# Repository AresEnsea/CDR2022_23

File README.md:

## Ce git contient les projets CubeIDE suivant : 
* Code pour F446RE principale utilisé à la coupe avec un bug pour la marche arrière "PhobosBoardWifiAndStratV2" 2A/Com/PhobosBoardWifiAndStratV2
* Code pour F446RE secondaire où la marche arrière fonctionne mais le code pour le lidar doit être ajouté "PhobosMainBoard" 2A/Com/PhobosMainBoard
* Code pour F303K8 gérant les actionneur "Project_Ax12" 2A/Project_Ax12
* Code pour G0 gérant le lidar "LIDAR_Ares_v1_4" 2A/Detection/LIDAR_Ares_v1_4
* Code pour F746 discovery kit de l'ihm "Final" 2A/Affichage/Final

## Le git est répartie en plusieurs fichiers :
* 2A/Com pour tout ce qui est lié à la communication sans fil
* 2A/Affichage pour l'ihm
*

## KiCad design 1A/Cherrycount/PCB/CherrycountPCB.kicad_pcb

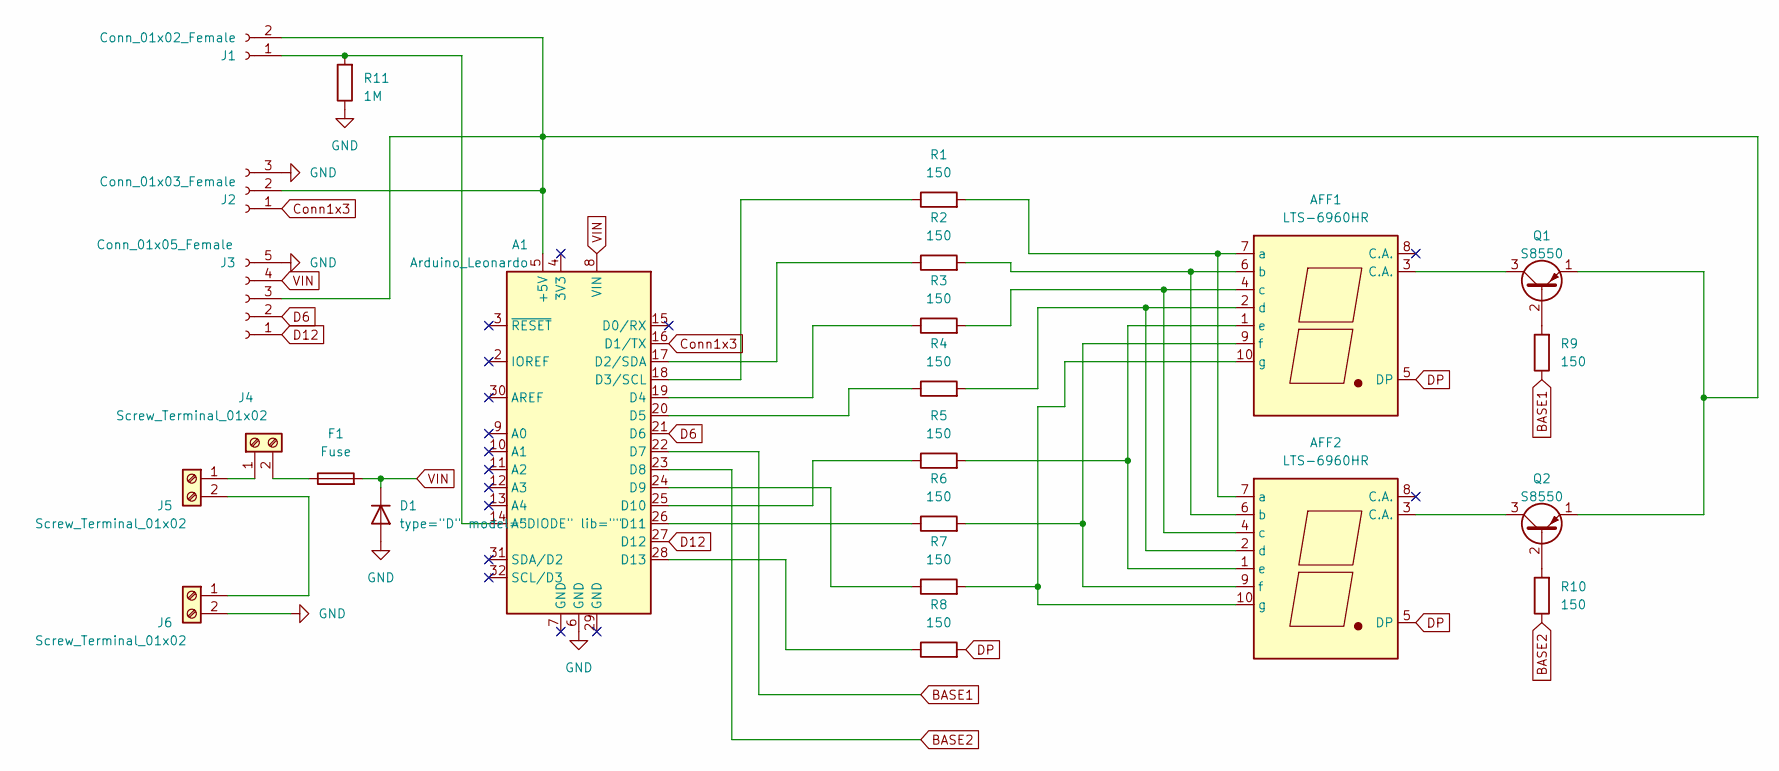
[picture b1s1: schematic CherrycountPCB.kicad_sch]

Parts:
A1: Arduino_Leonardo; Arduino_UNO_R3
AFF1, AFF2: LTS-6960HR; 7seg
D1: type="D" model="DIODE" lib=""; D_DO-41_SOD81_P7.62mm_Horizontal
F1: Fuse; polyswitch
J1: Conn_01x02_Female; PinHeader_1x02_P2.54mm_Vertical
J2: Conn_01x03_Female; PinHeader_1x03_P2.54mm_Vertical
J3: Conn_01x05_Female; PinHeader_1x05_P2.54mm_Vertical
J4, J5, J6: Screw_Terminal_01x02; 180G-2-vertical
Q1, Q2: S8550; TO-92_Inline
R1, R2, R3, R4, R5, R6, R7, R8, R9, R10: 150; R_0805_2012Metric_Pad1.20x1.40mm_HandSolder
R11: 1M; R_0805_2012Metric_Pad1.20x1.40mm_HandSolder

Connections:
BASE1: A1.22 (D7), R9.1
BASE2: A1.23 (D8), R10.1
Conn1x3: A1.16 (D1/TX), J2.1
D6: A1.21 (D6), J3.2
D12: A1.27 (D12), J3.1
DP: AFF1.5 (DP), AFF2.5 (DP), R8.2
GND: A1.6 (GND), D1.1 (A), J2.3, J3.5, J6.2, R11.1
unnamed: A1.5 (+5V), J1.2, J2.2, J3.3, Q1.1 (E), Q2.1 (E)
unnamed: A1.14 (A5), J1.1, R11.2
unnamed: A1.17 (D2/SDA), R2.1
unnamed: A1.18 (D3/SCL), R1.1
unnamed: A1.19 (D4), R3.1
unnamed: A1.20 (D5), R4.1
unnamed: A1.24 (D9), R7.1
unnamed: A1.25 (D10), R5.1
unnamed: A1.26 (D11), R6.1
unnamed: A1.28 (D13), R8.1
unnamed: AFF1.7 (a), AFF2.7 (a), R1.2
unnamed: AFF1.6 (b), AFF2.6 (b), R2.2
unnamed: AFF1.4 (c), AFF2.4 (c), R3.2
unnamed: AFF1.2 (d), AFF2.2 (d), R4.2
unnamed: AFF1.1 (e), AFF2.1 (e), R5.2
unnamed: AFF1.9 (f), AFF2.9 (f), R6.2
unnamed: AFF1.10 (g), AFF2.10 (g), R7.2
unnamed: J4.1, J5.1
unnamed: F1.1, J4.2
unnamed: J5.2, J6.1
unnamed: Q1.2 (B), R9.2
unnamed: AFF1.3 (C.A.), Q1.3 (C)
unnamed: Q2.2 (B), R10.2
unnamed: AFF2.3 (C.A.), Q2.3 (C)
VIN: A1.8 (VIN), D1.2 (K), F1.2, J3.4

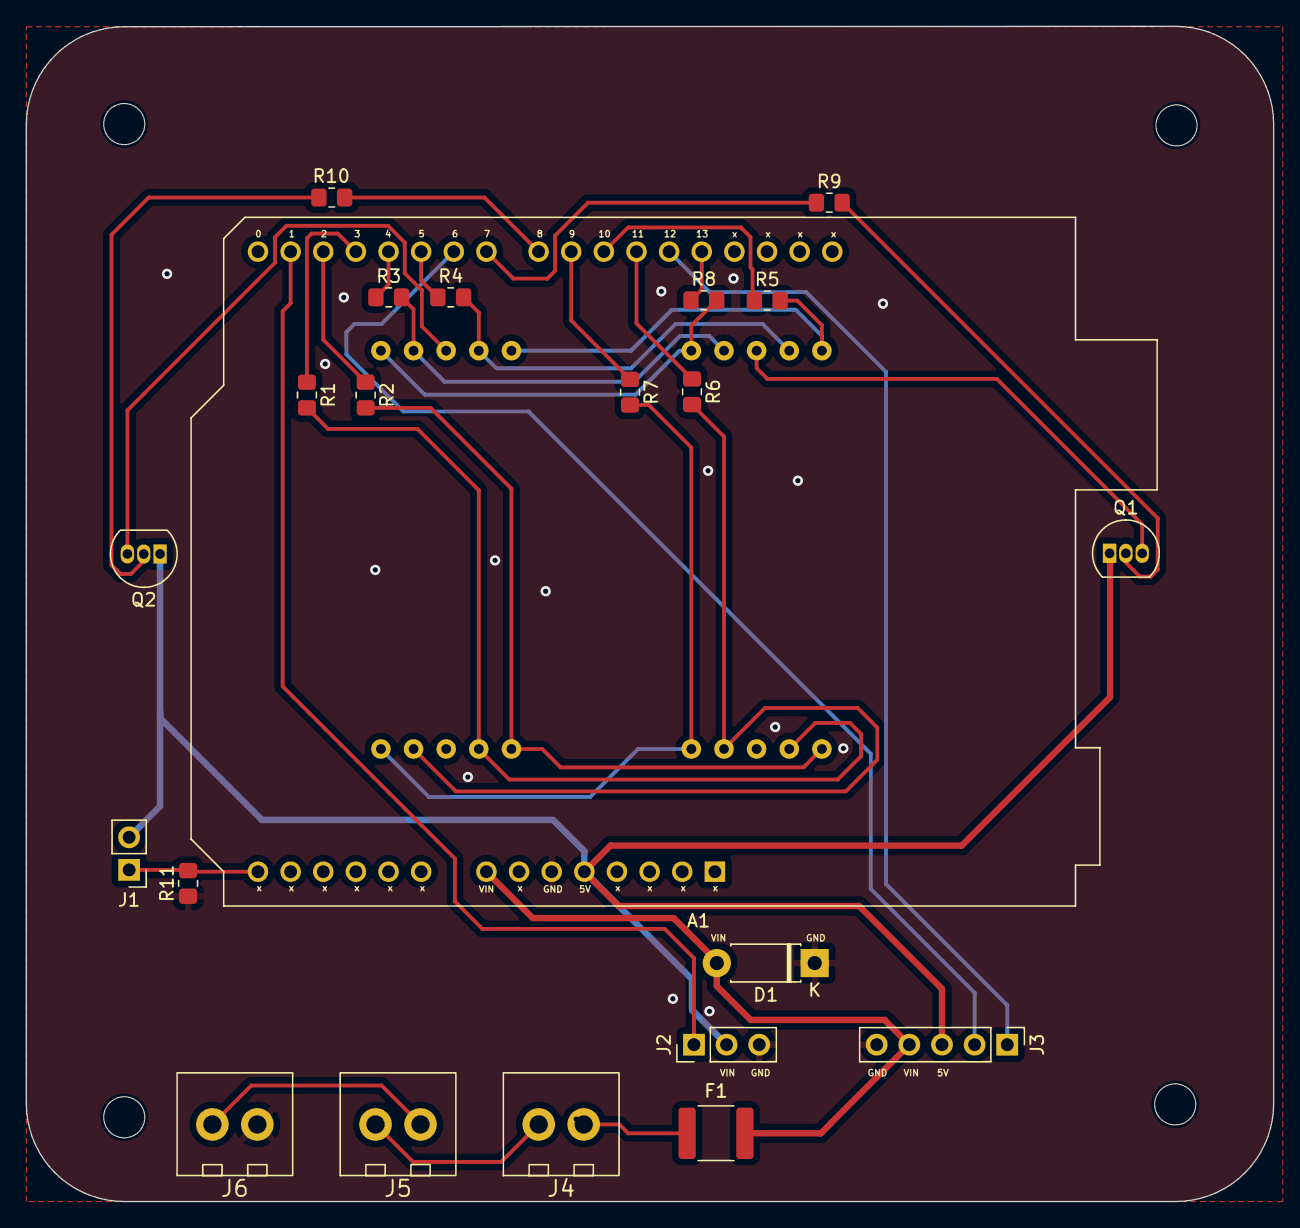
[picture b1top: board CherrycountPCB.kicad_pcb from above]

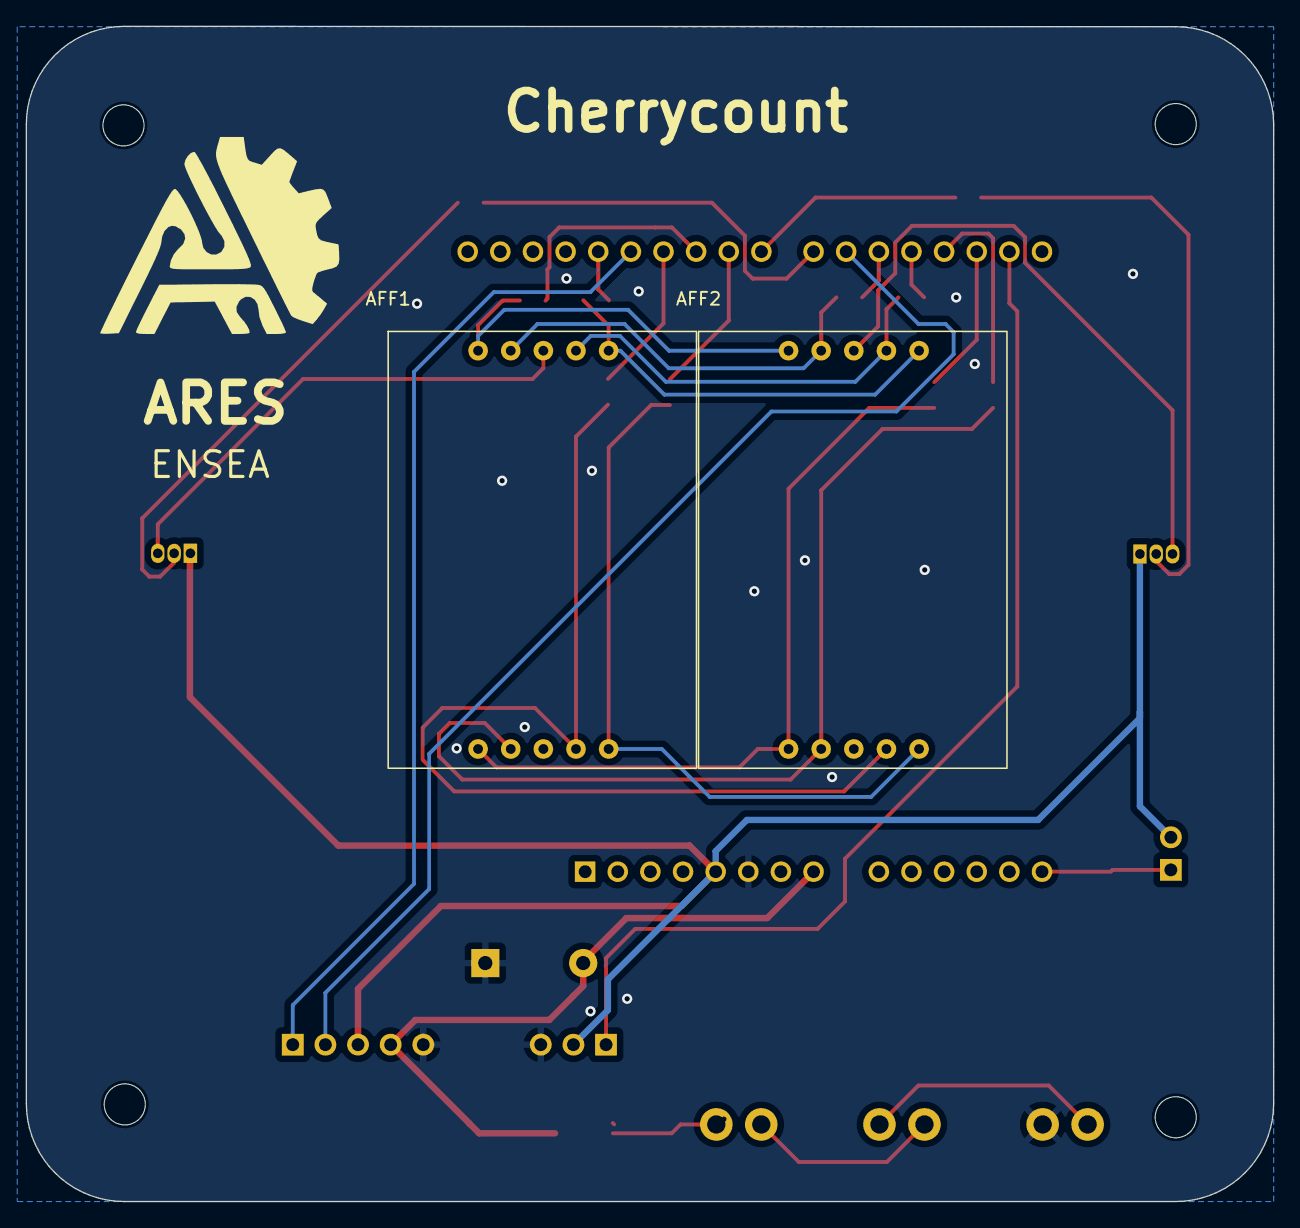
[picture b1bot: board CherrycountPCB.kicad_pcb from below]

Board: 2 copper layers, 97.1 x 91.5 mm, 24 parts (2 on the bottom side), 32 nets.

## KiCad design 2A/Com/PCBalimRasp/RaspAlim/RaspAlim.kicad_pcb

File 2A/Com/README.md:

## Instruction pour mettre en place le wifi
* Setup hotspot
* Setup ESP32
* Setup F446RE

## Setup hotspot :
L'ordinateur remplissant le rôle de hotspot doit :
*Respecter les dimensions imposés par le Coupe de France de Robotique pour le système de repérage
*Avoir une carte wifi émettant en 2.4GHz
*Pouvoir être alimenté par une battrie
Pour ces raison la raspberry Pi 4 à été choisis mais il existe plein d'alternative.

Pour configurer la rapsberry Pi 4 en hotspot il faut installer rasbpery Pi OS de préférence en 64 bits par soucis de compatibilité avec certaines librairies python.

Une fois le système installé et la rapsberry pi accessible par ssh ou VNC vous pouvez suivre ce tutoriel : https://www.youtube.com/watch?v=laeOmNDE-Ac&list=LL&index=231

Pour configurer l'hotspot exactement de la même manière que moi, un fichier txt contient ce que j'ai mis dans les différents fichiers de configuration de l'hotspot au chemin suivant 2A/Com/dhcpcd.txt

Une fois l'hotspot configuré vous pourrez faire fonctionner le serveur python au chemin 2A/Com/PythonServer/serverZMult.py

Ce serveur permet la communication entre robots quand le bit de poids fort est à 0. Il y a aussi une option debug qui peut être activée par les robots une fois connectée en Wi-Fi, cette option permet d'enregistrer un envoi de printf sur 10000 au log. Cela permet entre autres de renvoyer des données en continu comme la position et la distance de détection d'un obstacle sans surcharger la communication série de l'ESP32.

Pour envoyer des commandes au robot ou au serveur il faut passer par un autre fichier python client au chemin 2A/Com/PythonServer/client.py

Ce client est très basique, il peut permettre de lancer le robot à distance et d'arrêter ou relancer le debug. Le but de ce client à l'avenir et de renvoyer des informations issues d'un traitement d'images. 
## Setup ESP32 :

## Setup F446RE :

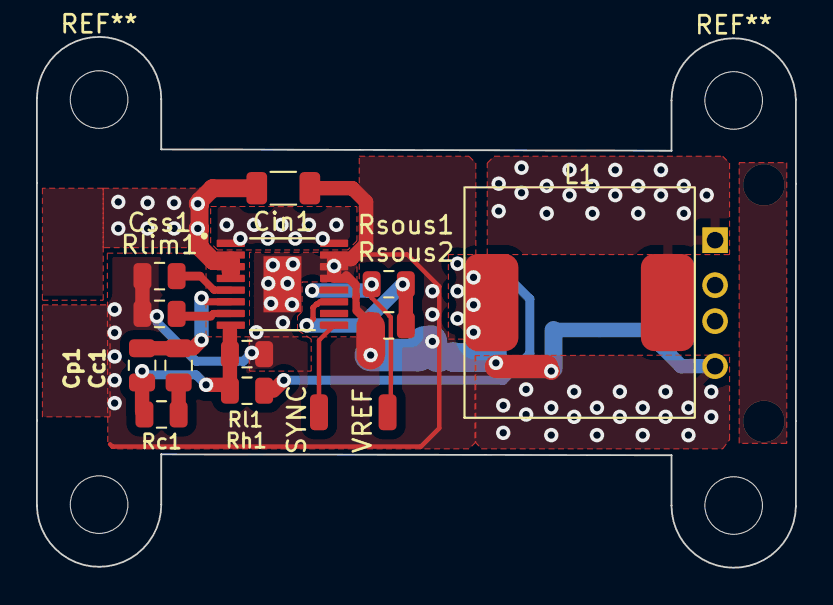
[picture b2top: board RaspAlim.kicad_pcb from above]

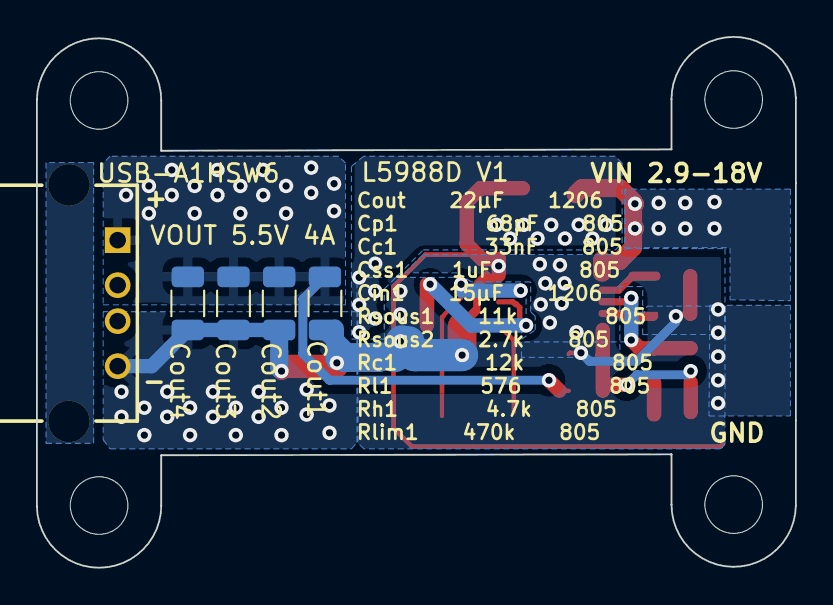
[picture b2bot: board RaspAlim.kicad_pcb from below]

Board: 2 copper layers, 42.2 x 29.5 mm, 19 parts (5 on the bottom side), 12 nets.

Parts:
Cc1: 33nF; C_0805_2012Metric
Cin1: 15µF; C_1206_3216Metric
Cout1, Cout2, Cout3, Cout4: 22µF; C_1206_3216Metric
Cp1: 68pF; C_0805_2012Metric
Css1: 1µF; C_0805_2012Metric
L1: 15µH; WE-PDA
P1: USB-A1HSW6; OST_USB-A1HSW6
Rc1: 12k; C_0805_2012Metric
Rh1: 4.7k; C_0805_2012Metric
Rl1: 576; C_0805_2012Metric
Rlim1: 470k; C_0805_2012Metric
Rsous1: 11k; C_0805_2012Metric
Rsous2: 2.7k; C_0805_2012Metric
SYNC: Conn_01x01_Pin; SolderWirePad_1x01_SMD_1x2mm
U1: L5988D
VREF: Conn_01x01_Pin; SolderWirePad_1x01_SMD_1x2mm

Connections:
/COMP: Cc1.1, Cp1.1, U1.6 (COMP)
/FB: Cp1.2, Rc1.2, Rh1.1, Rl1.2, U1.8 (FB)
/OUT: L1.1, U1.1 (OUT), U1.16 (OUT)
/Vbat: Cin1.1, U1.2 (VIN), U1.3 (VIN), U1.4 (VCC)
/Vout: Cout1.1, Cout2.1, Cout3.1, Cout4.1, L1.2, P1.1 (VBUS), Rh1.2
GNDPWR: Cin1.2, Cout1.2, Cout2.2, Cout3.2, Cout4.2, Css1.1, P1.4 (GND), Rl1.1, Rlim1.1, Rsous2.2, U1.13 (SGND), U1.14 (PGND), U1.15 (PGND), U1.17 (EP)
unnamed: Cc1.2, Rc1.1
unnamed: SYNC.1, U1.9 (SYNCH)
unnamed: Rsous1.1, U1.12 (VREF), VREF.1
unnamed: Rlim1.2, U1.7 (ILIM-ADJ)
unnamed: Css1.2, U1.5 (SS/INH#)
unnamed: Rsous1.2, Rsous2.1, U1.11 (U/O/S)

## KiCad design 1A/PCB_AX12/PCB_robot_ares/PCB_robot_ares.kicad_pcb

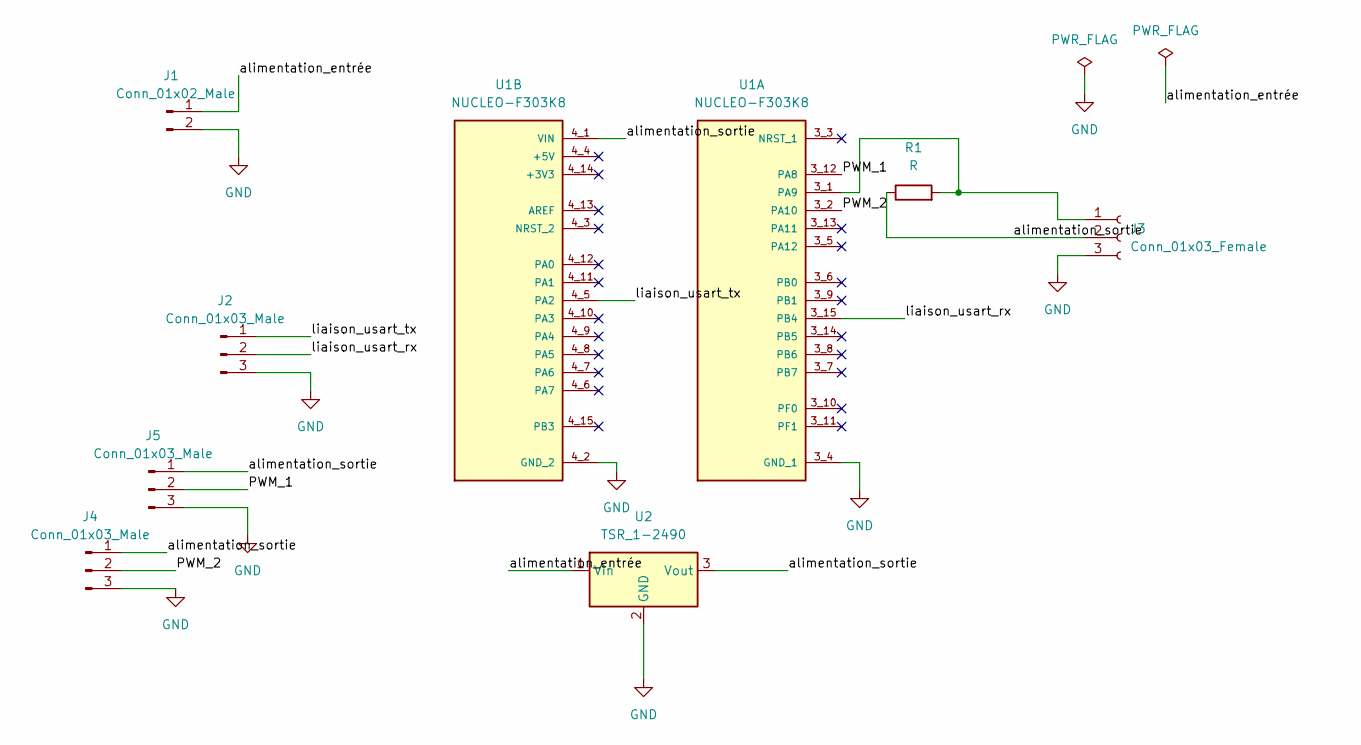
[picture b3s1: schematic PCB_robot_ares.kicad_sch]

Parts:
J1: Conn_01x02_Male; PinHeader_1x02_P2.54mm_Vertical
J2, J4, J5: Conn_01x03_Male; PinHeader_1x03_P2.54mm_Vertical
J3: Conn_01x03_Female; PinSocket_1x03_P2.54mm_Vertical
R1: R; R_0805_2012Metric
U1: NUCLEO-F303K8; MODULE_NUCLEO-F303K8; PARTREV 5
U2: TSR_1-2490; Converter_DCDC_TRACO_TSR-1_THT

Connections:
/PWM_1: J5.2, U1.3_12 (PA8)
/PWM_2: J4.2, U1.3_2 (PA10)
/alimentation_entrée: J1.1, U2.1 (Vin)
/alimentation_sortie: J3.2, J4.1, J5.1, R1.1, U1.4_1 (VIN), U2.3 (Vout)
/liaison_usart_rx: J2.2, U1.3_15 (PB4)
/liaison_usart_tx: J2.1, U1.4_5 (PA2)
GND: J1.2, J2.3, J3.3, J4.3, J5.3, U1.3_4 (GND_1), U1.4_2 (GND_2), U2.2 (GND)
unnamed: J3.1, R1.2, U1.3_1 (PA9)

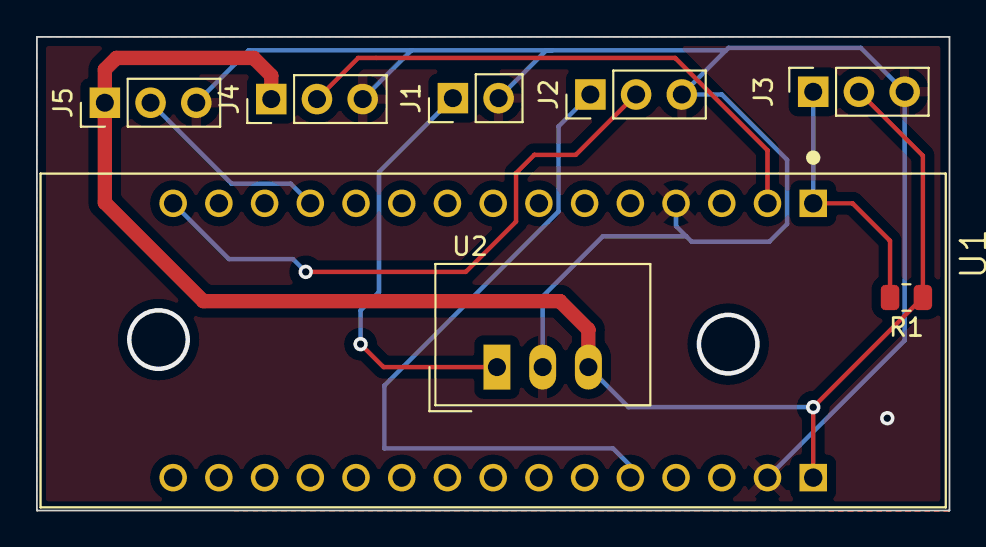
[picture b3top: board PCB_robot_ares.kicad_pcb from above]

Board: 2 copper layers, 50.7 x 26.3 mm, 8 parts (0 on the bottom side), 8 nets.

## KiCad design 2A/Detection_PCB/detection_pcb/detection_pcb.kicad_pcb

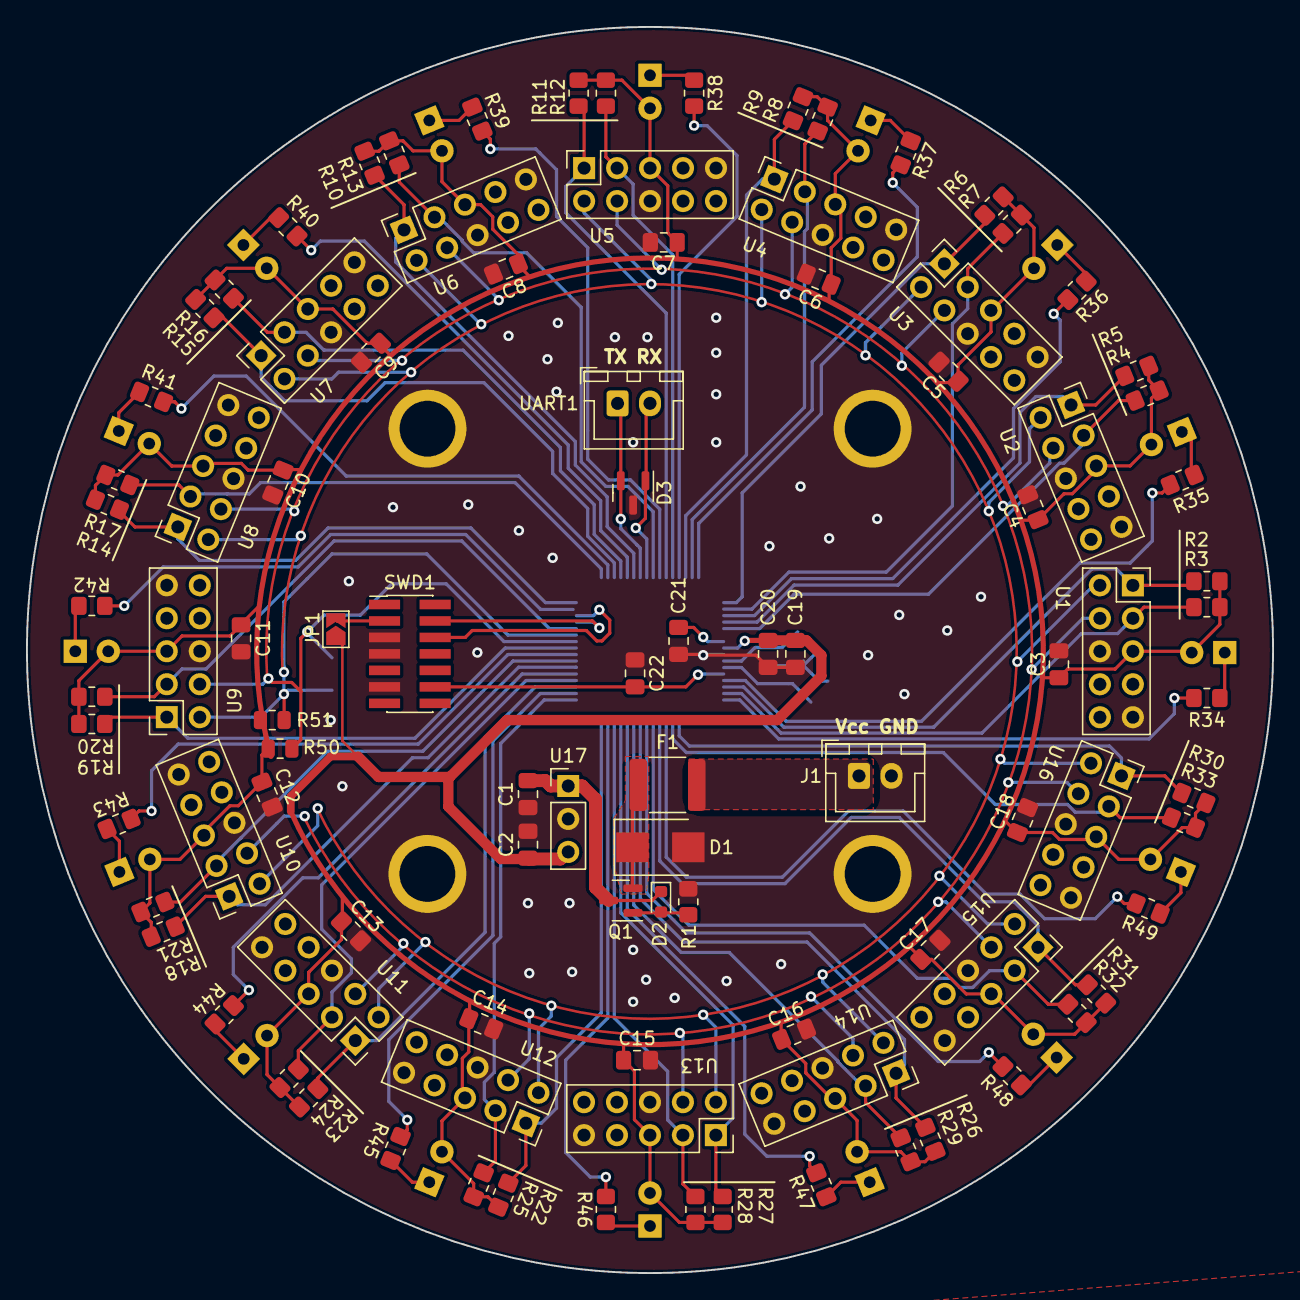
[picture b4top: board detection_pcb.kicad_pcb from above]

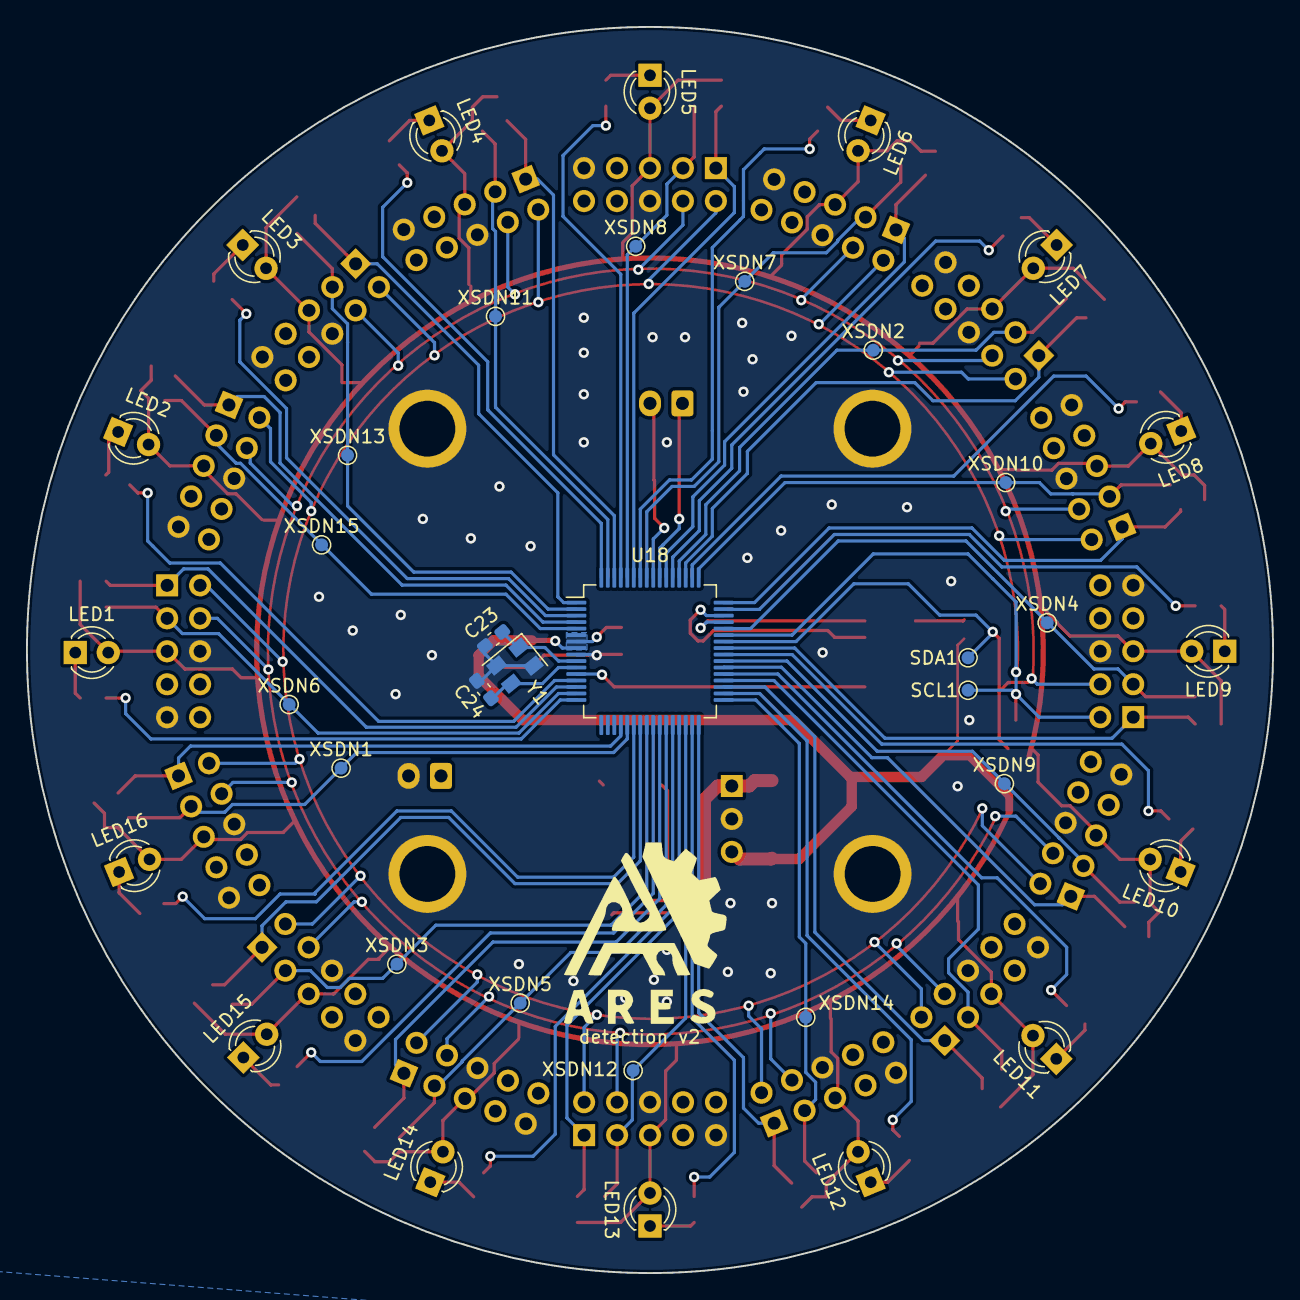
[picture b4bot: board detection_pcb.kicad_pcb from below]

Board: 2 copper layers, 96.0 x 96.0 mm, 140 parts (37 on the bottom side), 80 nets.

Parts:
C1: 22u; C_0805_2012Metric_Pad1.18x1.45mm_HandSolder
C2: 10u; C_0805_2012Metric_Pad1.18x1.45mm_HandSolder
C3, C4, C5, C6, C7, C8, C9, C10, C11, C12, C13, C14, C15, C16, C17, C18: 1u; C_0805_2012Metric_Pad1.18x1.45mm_HandSolder
C19: 4.7u; C_0805_2012Metric_Pad1.18x1.45mm_HandSolder
C20, C21, C22: 100n; C_0805_2012Metric_Pad1.18x1.45mm_HandSolder
C23, C24: 20p; C_0603_1608Metric_Pad1.08x0.95mm_HandSolder
D1: SM6T24A; D_SMB
D2: 10V; D_0603_1608Metric
D3: NUP2105L; SOT-23
F1: polyfuse; polyswitch
H1, H2, H3, H4: MountingHole_Pad; MountingHole_4.3mm_M4_DIN965_Pad
J1: BAT; JST_XH_B2B-XH-A_1x02_P2.50mm_Vertical
JP1: SolderJumper_2_Open; SolderJumper-2_P1.3mm_Open_TrianglePad1.0x1.5mm
LED1, LED2, LED3, LED4, LED5, LED6, LED7, LED8, LED9, LED10, LED11, LED12, LED13, LED14, LED15, LED16: LED; LED_D3.0mm
Q1: PMOS; SOT-23
R1, R2, R3, R4, R5, R6, R7, R8, R9, R10, R11, R12, R13, R14, R15, R16, R17, R18, R19, R20, R21, R22, R23, R24, R25, R26, R27, R28, R29, R30, R31, R32, R33: 10k; R_0805_2012Metric_Pad1.20x1.40mm_HandSolder
R34, R35, R36, R37, R38, R39, R40, R41, R42, R43, R44, R45, R46, R47, R48, R49: 3k; R_0805_2012Metric_Pad1.20x1.40mm_HandSolder
R50, R51: 2.2k; R_0805_2012Metric
SCL1: TestPoint; TestPoint_Pad_D1.0mm
SDA1: TestPoint; TestPoint_Pad_D1.0mm
SWD1: Conn_02x07_Odd_Even; PinHeader_2x07_P1.27mm_Vertical_SMD
U1, U2, U3, U4, U5, U6, U7, U8, U9, U10, U11, U12, U13, U14, U15, U16: VL53L1X_module; PinHeader_2x05_P2.54mm_Vertical
U17: Buck_3.3V; PinHeader_1x03_P2.54mm_Vertical
U18: STM32G070; LQFP-64_10x10mm_P0.5mm
UART1: Conn_01x02_Male; JST_XH_B2B-XH-A_1x02_P2.50mm_Vertical
XSDN1, XSDN2, XSDN3, XSDN4, XSDN5, XSDN6, XSDN7, XSDN8, XSDN9, XSDN10, XSDN11, XSDN12, XSDN13, XSDN14, XSDN15: TestPoint; TestPoint_Pad_D1.0mm
Y1: 16MHz; Crystal_SMD_EuroQuartz_MT-4Pin_3.2x2.5mm

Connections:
+3V3: C2.1, C3.1, C4.1, C5.1, C6.1, C7.1, C8.1, C9.1, C10.1, C11.1, C12.1, C13.1, C14.1, C15.1, C16.1, C17.1, C18.1, C19.1, C20.1, C21.1, JP1.1 (A), LED1.2 (A), LED2.2 (A), LED3.2 (A), LED4.2 (A), LED5.2 (A), LED6.2 (A), LED7.2 (A), LED8.2 (A), LED9.2 (A), LED10.2 (A), LED11.2 (A), LED12.2 (A), LED13.2 (A), LED14.2 (A), LED15.2 (A), LED16.2 (A), R2.2, R3.2, R4.2, R5.2, R6.2, R7.2, R8.2, R9.2, R10.2, R11.2, R12.2, R13.2, R14.2, R15.2, R16.2, R17.2, R18.2, R19.2, R20.2, R21.2, R22.2, R23.2, R24.2, R25.2, R26.2, R27.2, R28.2, R29.2, R30.2, R31.2, R32.2, R33.2, R50.1, R51.2, U1.5 (VDD), U2.5 (VDD), U3.5 (VDD), U4.5 (VDD), U5.5 (VDD), U6.5 (VDD), U7.5 (VDD), U8.5 (VDD), U9.5 (VDD), U10.5 (VDD), U11.5 (VDD), U12.5 (VDD), U13.5 (VDD), U14.5 (VDD), U15.5 (VDD), U16.5 (VDD), U17.3 (VOUT), U18.6 (VBAT), U18.7 (VREF+), U18.8 (VDD/VDDA)
GND: C1.2, C2.2, C3.2, C4.2, C5.2, C6.2, C7.2, C8.2, C9.2, C10.2, C11.2, C12.2, C13.2, C14.2, C15.2, C16.2, C17.2, C18.2, C19.2, C20.2, C21.2, C22.1, C23.2, C24.2, D1.2 (A2), D3.3 (A), H1.1, H2.1, H3.1, H4.1, J1.2, R1.2, SWD1.5, SWD1.7, SWD1.11, U1.6 (GND), U1.9 (NC1), U2.6 (GND), U2.9 (NC1), U3.6 (GND), U3.9 (NC1), U4.6 (GND), U4.9 (NC1), U5.6 (GND), U5.9 (NC1), U6.6 (GND), U6.9 (NC1), U7.6 (GND), U7.9 (NC1), U8.6 (GND), U8.9 (NC1), U9.6 (GND), U9.9 (NC1), U10.6 (GND), U10.9 (NC1), U11.6 (GND), U11.9 (NC1), U12.6 (GND), U12.9 (NC1), U13.6 (GND), U13.9 (NC1), U14.6 (GND), U14.9 (NC1), U15.6 (GND), U15.9 (NC1), U16.6 (GND), U16.9 (NC1), U17.2 (GND), U18.9 (VSS/VSSA), Y1.2, Y1.4
INT0: R2.1, U1.1 (INT), U18.14 (PC1)
INT1: R5.1, U2.1 (INT), U18.4 (PC14)
INT2: R6.1, U3.1 (INT), U18.1 (PC11)
INT3: R9.1, U4.1 (INT), U18.62 (PB8)
INT4: R11.1, U5.1 (INT), U18.59 (PB5)
INT5: R10.1, U6.1 (INT), U18.54 (PD4)
INT6: R15.1, U7.1 (INT), U18.51 (PD1)
INT7: R14.1, U8.1 (INT), U18.48 (PC8)
INT8: R19.1, U9.1 (INT), U18.41 (PD9)
INT9: R18.1, U10.1 (INT), U18.38 (PC6)
INT10: R23.1, U11.1 (INT), U18.35 (PB15)
INT11: R22.1, U12.1 (INT), U18.32 (PB12)
INT12: R27.1, U13.1 (INT), U18.29 (PB2)
INT13: R26.1, U14.1 (INT), U18.26 (PC5)
INT14: R31.1, U15.1 (INT), U18.23 (PA6)
INT15: R30.1, U16.1 (INT), U18.20 (PA3)
LED0: R34.1, U18.16 (PC3)
LED1: R35.2, U18.13 (PC0)
LED2: R36.2, U18.3 (PC13)
LED3: R37.2, U18.64 (PC10)
LED4: R38.2, U18.61 (PB7)
LED5: R39.2, U18.58 (PB4)
LED6: R40.2, U18.53 (PD3)
LED7: R41.2, U18.50 (PD0)
LED8: R42.2, U18.47 (PA15)
LED9: R43.2, U18.40 (PD8)
LED10: R44.2, U18.37 (PA9)
LED11: R45.2, U18.34 (PB14)
LED12: R46.2, U18.31 (PB11)
LED13: R47.2, U18.28 (PB1)
LED14: R48.2, U18.25 (PC4)
LED15: R49.2, U18.22 (PA5)
NRST: C22.2, SWD1.12, U18.12 (NRST)
unnamed: C1.1, D2.1 (K), Q1.3 (S), U17.1 (VIN)
unnamed: C23.1, U18.10 (PF0), Y1.1
unnamed: C24.1, U18.11 (PF1), Y1.3
unnamed: D1.1 (A1), F1.1, Q1.2 (D)
unnamed: D2.2 (A), Q1.1 (G), R1.1
unnamed: F1.2, J1.1
unnamed: JP1.2 (B), SWD1.3
unnamed: LED1.1 (K), R34.2
unnamed: LED2.1 (K), R35.1
unnamed: LED3.1 (K), R36.1
unnamed: LED4.1 (K), R37.1
unnamed: LED5.1 (K), R38.1
unnamed: LED6.1 (K), R39.1
unnamed: LED7.1 (K), R40.1
unnamed: LED8.1 (K), R41.1
unnamed: LED9.1 (K), R42.1
unnamed: LED10.1 (K), R43.1
unnamed: LED11.1 (K), R44.1
unnamed: LED12.1 (K), R45.1
unnamed: LED13.1 (K), R46.1
unnamed: LED14.1 (K), R47.1
unnamed: LED15.1 (K), R48.1
unnamed: LED16.1 (K), R49.1
RX: D3.1 (K), U18.56 (PD6), UART1.2
SCL: R51.1, SCL1.1, U1.2 (SCL), U2.2 (SCL), U3.2 (SCL), U4.2 (SCL), U5.2 (SCL), U6.2 (SCL), U7.2 (SCL), U8.2 (SCL), U9.2 (SCL), U10.2 (SCL), U11.2 (SCL), U12.2 (SCL), U13.2 (SCL), U14.2 (SCL), U15.2 (SCL), U16.2 (SCL), U18.43 (PA11)
SDA: R50.2, SDA1.1, U1.4 (SDA), U2.4 (SDA), U3.4 (SDA), U4.4 (SDA), U5.4 (SDA), U6.4 (SDA), U7.4 (SDA), U8.4 (SDA), U9.4 (SDA), U10.4 (SDA), U11.4 (SDA), U12.4 (SDA), U13.4 (SDA), U14.4 (SDA), U15.4 (SDA), U16.4 (SDA), U18.42 (PA10)
SWCLK: SWD1.6, U18.46 (BOOT0-PA14)
SWDIO: SWD1.4, U18.45 (PA13)
TX: D3.2 (K), U18.55 (PD5), UART1.1
XSDN0: R3.1, U1.3 (XSDN), U18.15 (PC2), XSDN6.1
XSDN1: R4.1, U2.3 (XSDN), U18.5 (PC15), XSDN15.1
XSDN2: R7.1, U3.3 (XSDN), U18.2 (PC12), XSDN13.1
XSDN3: R8.1, U4.3 (XSDN), U18.63 (PB9), XSDN11.1
XSDN4: R12.1, U5.3 (XSDN), U18.60 (PB6), XSDN8.1
XSDN5: R13.1, U6.3 (XSDN), U18.57 (PB3), XSDN7.1
XSDN6: R16.1, U7.3 (XSDN), U18.52 (PD2), XSDN2.1
XSDN7: R17.1, U8.3 (XSDN), U18.49 (PC9), XSDN10.1
XSDN8: R20.1, U9.3 (XSDN), U18.44 (PA12), XSDN4.1
XSDN9: R21.1, U10.3 (XSDN), U18.39 (PC7), XSDN9.1
XSDN10: R24.1, U11.3 (XSDN), U18.36 (PA8)
XSDN11: R25.1, U12.3 (XSDN), U18.33 (PB13), XSDN14.1
XSDN12: R28.1, U13.3 (XSDN), U18.30 (PB10), XSDN12.1
XSDN13: R29.1, U14.3 (XSDN), U18.27 (PB0), XSDN5.1
XSDN14: R32.1, U15.3 (XSDN), U18.24 (PA7), XSDN3.1
XSDN15: R33.1, U16.3 (XSDN), U18.21 (PA4), XSDN1.1

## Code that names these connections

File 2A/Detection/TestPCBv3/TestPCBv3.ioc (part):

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Mcu.Name=STM32G070RBTx
Mcu.Package=LQFP64
Mcu.UserName=STM32G070RBTx
PA10.Mode=I2C
PA10.Signal=I2C1_SDA
PA12\ [PA10].Signal=GPIO_Output
PA15.Signal=GPIO_Output
PA4.Signal=GPIO_Output
PA5.Signal=GPIO_Output
PA7.Signal=GPIO_Output
PA8.Signal=GPIO_Output
PA9.Mode=I2C
PA9.Signal=I2C1_SCL
PB0.Signal=GPIO_Output
PB1.Signal=GPIO_Output
PB10.Signal=GPIO_Output
PB11.Signal=GPIO_Output
PB13.Signal=GPIO_Output
PB14.Signal=GPIO_Output
PB3.Signal=GPIO_Output
PB4.Signal=GPIO_Output
PB6.Signal=GPIO_Output
PB7.Signal=GPIO_Output
PB9.Signal=GPIO_Output
PC0.Signal=GPIO_Output
PC10.Signal=GPIO_Output
PC12.Signal=GPIO_Output
PC13.Signal=GPIO_Output
PC15-OSC32_OUT\ (PC15).Signal=GPIO_Output
PC2.Signal=GPIO_Output
PC3.Signal=GPIO_Output
PC4.Signal=GPIO_Output
PC7.Signal=GPIO_Output
PC9.Signal=GPIO_Output
PD0.Signal=GPIO_Output
PD2.Signal=GPIO_Output
PD3.Signal=GPIO_Output
PD5.Mode=Asynchronous
PD5.Signal=USART2_TX
PD6.Mode=Asynchronous
PD6.Signal=USART2_RX
PD8.Signal=GPIO_Output
PF0-OSC_IN\ (PF0).Mode=HSE-External-Oscillator
PF0-OSC_IN\ (PF0).Signal=RCC_OSC_IN
PF1-OSC_OUT\ (PF1).Mode=HSE-External-Oscillator
PF1-OSC_OUT\ (PF1).Signal=RCC_OSC_OUT
RCC.HSE_VALUE=16000000
RCC.SYSCLKFreq_VALUE=64000000
RCC.SYSCLKSource=RCC_SYSCLKSOURCE_PLLCLK
board=custom

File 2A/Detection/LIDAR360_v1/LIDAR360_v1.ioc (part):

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Mcu.Name=STM32F410R(8-B)Tx
Mcu.Package=LQFP64
Mcu.UserName=STM32F410RBTx
PA13.GPIOParameters=GPIO_Label
PA13.GPIO_Label=TMS
PA13.Mode=Serial_Wire
PA13.Signal=SYS_JTMS-SWDIO
PA14.GPIOParameters=GPIO_Label
PA14.GPIO_Label=TCK
PA14.Mode=Serial_Wire
PA14.Signal=SYS_JTCK-SWCLK
PA2.GPIOParameters=GPIO_Label
PA2.GPIO_Label=USART_TX
PA2.Mode=Asynchronous
PA2.Signal=USART2_TX
PA3.GPIOParameters=GPIO_Label
PA3.GPIO_Label=USART_RX
PA3.Mode=Asynchronous
PA3.Signal=USART2_RX
PA5.GPIOParameters=GPIO_Label
PA5.GPIO_Label=LD2 [Green Led]
PA5.Signal=GPIO_Output
PB0.Signal=GPIO_Output
PB1.Signal=GPIO_Output
PB2.Signal=GPIO_Output
PB3.GPIOParameters=GPIO_Label
PB3.GPIO_Label=SWO
PB3.Signal=SYS_JTDO-SWO
PB4.Signal=GPIO_Output
PB5.Signal=GPIO_Output
PB6.Mode=I2C
PB6.Signal=I2C1_SCL
PB7.Mode=I2C
PB7.Signal=I2C1_SDA
PB8.Signal=GPXTI8
PB9.Signal=GPIO_Output
PC10.Signal=GPIO_Output
PC11.Signal=GPIO_Output
PC12.Signal=GPIO_Output
PC13-ANTI_TAMP.GPIOParameters=GPIO_Label,GPIO_ModeDefaultEXTI
PC13-ANTI_TAMP.GPIO_Label=B1 [Blue PushButton]
PC13-ANTI_TAMP.GPIO_ModeDefaultEXTI=GPIO_MODE_IT_FALLING
PC13-ANTI_TAMP.Signal=GPXTI13
PC14-OSC32_IN.Mode=LSE-External-Oscillator
PC14-OSC32_IN.Signal=RCC_OSC32_IN
PC15-OSC32_OUT.Mode=LSE-External-Oscillator
PC15-OSC32_OUT.Signal=RCC_OSC32_OUT
PC2.Signal=GPIO_Output
PC3.Signal=GPIO_Output
PC4.Signal=GPIO_Output
PC5.Signal=GPIO_Output
PC6.Signal=GPIO_Output
PC7.Signal=GPIO_Output
PC8.Signal=GPIO_Output
PC9.Signal=GPIO_Output
PH0\ -\ OSC_IN.Mode=HSE-External-Clock-Source
PH0\ -\ OSC_IN.Signal=RCC_OSC_IN
PH1\ -\ OSC_OUT.Mode=HSE-External-Clock-Source
PH1\ -\ OSC_OUT.Signal=RCC_OSC_OUT
RCC.HSE_VALUE=8000000
RCC.SYSCLKFreq_VALUE=84000000
RCC.SYSCLKSource=RCC_SYSCLKSOURCE_PLLCLK
board=NUCLEO-F410RB

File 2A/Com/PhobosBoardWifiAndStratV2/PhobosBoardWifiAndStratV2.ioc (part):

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Mcu.Name=STM32F446R(C-E)Tx
Mcu.Package=LQFP64
Mcu.UserName=STM32F446RETx
PA0-WKUP.Mode=Asynchronous
PA0-WKUP.Signal=UART4_TX
PA1.Mode=Asynchronous
PA1.Signal=UART4_RX
PA10.Mode=Asynchronous
PA10.Signal=USART1_RX
PA2.Mode=Asynchronous
PA2.Signal=USART2_TX
PA3.Mode=Asynchronous
PA3.Signal=USART2_RX
PA4.GPIOParameters=GPIO_Label
PA4.GPIO_Label=TrigServo
PA4.Signal=GPIO_Output
PA5.GPIOParameters=GPIO_Label
PA5.GPIO_Label=GREEN_LED
PA5.Signal=GPIO_Output
PA6.GPIOParameters=GPIO_Label
PA6.GPIO_Label=L_ENCODER_A
PA6.Signal=S_TIM3_CH1
PA7.GPIOParameters=GPIO_Label
PA7.GPIO_Label=L_ENCODER_B
PA7.Signal=S_TIM3_CH2
PA8.GPIOParameters=GPIO_Label
PA8.GPIO_Label=R_ENCODER_A
PA8.Signal=S_TIM1_CH1
PA9.GPIOParameters=GPIO_Label
PA9.GPIO_Label=R_ENCODER_B
PA9.Signal=S_TIM1_CH2
PB0.GPIOParameters=GPIO_Label
PB0.GPIO_Label=WIFI_STATE
PB0.Signal=GPIO_Input
PB6.Mode=Asynchronous
PB6.Signal=USART1_TX
PB8.GPIOParameters=GPIO_Label
PB8.GPIO_Label=TEAM_LED
PB8.Signal=GPIO_Output
PB9.Signal=S_TIM11_CH1
PC0.GPIOParameters=GPIO_Label
PC0.GPIO_Label=L_MOTOR_EN
PC0.Signal=GPIO_Output
PC1.GPIOParameters=GPIO_Label
PC1.GPIO_Label=R_MOTOR_EN
PC1.Signal=GPIO_Output
PC11.GPIOParameters=GPIO_Label
PC11.GPIO_Label=R_MOTOR_DIR
PC11.Signal=GPIO_Output
PC12.Mode=Asynchronous
PC12.Signal=UART5_TX
PC2.GPIOParameters=GPIO_Label
PC2.GPIO_Label=L_MOTOR_DIR
PC2.Signal=GPIO_Output
PC6.Mode=Asynchronous
PC6.Signal=USART6_TX
PC7.Mode=Asynchronous
PC7.Signal=USART6_RX
PC8.GPIOParameters=GPIO_PuPd,GPIO_Label
PC8.GPIO_Label=START
PC8.GPIO_PuPd=GPIO_PULLDOWN
PC8.Signal=GPIO_Input
PC9.Signal=S_TIM8_CH4
PD2.Mode=Asynchronous
PD2.Signal=UART5_RX
RCC.HSE_VALUE=8000000
RCC.SYSCLKFreq_VALUE=180000000
RCC.SYSCLKSource=RCC_SYSCLKSOURCE_PLLCLK
board=NUCLEO-F446RE
boardIOC=true

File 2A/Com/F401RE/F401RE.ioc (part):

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Mcu.Name=STM32F401R(D-E)Tx
Mcu.Package=LQFP64
Mcu.UserName=STM32F401RETx
PA10.Mode=Asynchronous
PA10.Signal=USART1_RX
PA13.GPIOParameters=GPIO_Label
PA13.GPIO_Label=TMS
PA13.Mode=Serial_Wire
PA13.Signal=SYS_JTMS-SWDIO
PA14.GPIOParameters=GPIO_Label
PA14.GPIO_Label=TCK
PA14.Mode=Serial_Wire
PA14.Signal=SYS_JTCK-SWCLK
PA2.GPIOParameters=GPIO_Speed,GPIO_PuPd,GPIO_Label,GPIO_Mode
PA2.GPIO_Label=USART_TX
PA2.GPIO_Mode=GPIO_MODE_AF_PP
PA2.GPIO_PuPd=GPIO_NOPULL
PA2.GPIO_Speed=GPIO_SPEED_FREQ_LOW
PA2.Mode=Asynchronous
PA2.Signal=USART2_TX
PA3.GPIOParameters=GPIO_Speed,GPIO_PuPd,GPIO_Label,GPIO_Mode
PA3.GPIO_Label=USART_RX
PA3.GPIO_Mode=GPIO_MODE_AF_PP
PA3.GPIO_PuPd=GPIO_NOPULL
PA3.GPIO_Speed=GPIO_SPEED_FREQ_LOW
PA3.Mode=Asynchronous
PA3.Signal=USART2_RX
PA5.GPIOParameters=GPIO_Speed,GPIO_PuPd,GPIO_Label,GPIO_Mode
PA5.GPIO_Label=LD2 [Green Led]
PA5.GPIO_Mode=GPIO_MODE_OUTPUT_PP
PA5.GPIO_PuPd=GPIO_NOPULL
PA5.GPIO_Speed=GPIO_SPEED_FREQ_LOW
PA5.Signal=GPIO_Output
PA9.Mode=Asynchronous
PA9.Signal=USART1_TX
PB12.GPIOParameters=GPIO_Speed,GPIO_Label
PB12.GPIO_Label=LCD_RST
PB12.GPIO_Speed=GPIO_SPEED_FREQ_LOW
PB12.Signal=GPIO_Output
PB14.GPIOParameters=GPIO_Speed,GPIO_Label
PB14.GPIO_Label=LCD_RS
PB14.GPIO_Speed=GPIO_SPEED_FREQ_LOW
PB14.Signal=GPIO_Output
PB15.GPIOParameters=GPIO_Speed,GPIO_Label
PB15.GPIO_Label=LCD_CS
PB15.GPIO_Speed=GPIO_SPEED_FREQ_LOW
PB15.Signal=GPIO_Output
PB3.Mode=TX_Only_Simplex_Unidirect_Master
PB3.Signal=SPI1_SCK
PB5.Mode=TX_Only_Simplex_Unidirect_Master
PB5.Signal=SPI1_MOSI
PC13-ANTI_TAMP.GPIOParameters=GPIO_PuPd,GPIO_Label,GPIO_ModeDefaultEXTI
PC13-ANTI_TAMP.GPIO_Label=B1 [Blue PushButton]
PC13-ANTI_TAMP.GPIO_ModeDefaultEXTI=GPIO_MODE_IT_FALLING
PC13-ANTI_TAMP.GPIO_PuPd=GPIO_NOPULL
PC13-ANTI_TAMP.Signal=GPXTI13
PC14-OSC32_IN.Mode=LSE-External-Oscillator
PC14-OSC32_IN.Signal=RCC_OSC32_IN
PC15-OSC32_OUT.Mode=LSE-External-Oscillator
PC15-OSC32_OUT.Signal=RCC_OSC32_OUT
PH0\ -\ OSC_IN.Mode=HSE-External-Clock-Source
PH0\ -\ OSC_IN.Signal=RCC_OSC_IN
PH1\ -\ OSC_OUT.Mode=HSE-External-Clock-Source
PH1\ -\ OSC_OUT.Signal=RCC_OSC_OUT
RCC.HSE_VALUE=8000000
RCC.SYSCLKFreq_VALUE=84000000
RCC.SYSCLKSource=RCC_SYSCLKSOURCE_PLLCLK
board=NUCLEO-F401RE
boardIOC=true

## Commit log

2022-09-27 test
2022-09-27 le fun d'utiliser github
2022-09-27 commentaire
2022-09-27 pourmoi
2022-09-29 fichier 1A
2022-09-29 test Aliou
2022-09-29 txt deletation
2022-09-29 new set
2022-09-30 news doc git
2022-10-03 prog test esp
2022-10-04 Creation categorie detection
2022-10-04 com up
2022-10-06 Test timer
2022-10-06 Test LED
2022-10-11 new code server
2022-10-11 programme afichage V1
2022-10-12 OS fonctionnant avec 2 taches
2022-10-14 add gitignore
2022-10-14 gitignorKiCADST
2022-10-15 gitignore2
2022-10-18 usart utile
2022-10-18 calculateur de points renvoyant dans luart
2022-10-22 comSelectV1
2022-10-22 Stm32emit
2022-11-03 Tothelast
2022-11-05 comOk
2022-11-10 lecture du des donnees de la teensy
2022-11-15 1stOk
2022-11-15 dams
2022-11-15 Systeme de detection pour STM32
2022-11-15 suppression pcb
2022-11-15 ajout pcb
2022-11-20 siiin
2022-11-28 ajoutCoderobot
2022-12-01 filtre
2022-12-06 Adaptation LIDAR 2D de ST
2022-12-06 comPos
2022-12-11 next version
2022-12-13 2esp
2022-12-15 Ajout de la detection de position aruco v1
    langage python, supposé marcher sur raspi avec caméra
2022-12-16 joinedStartup
2023-01-03 programme afichage V2
2023-01-03 Lidar fonctionnant avec un failble rafraichissement
2023-01-03 score
2023-01-08 Affichage fini
2023-01-19 multiplexagesSockets
2023-01-20 rasp
2023-01-24 Affichage Final
2023-01-30 Modification du PCB du compteur de cerises
2023-01-31 updateEsp
2023-01-31 avancerrobot
2023-01-31 miseajour
2023-01-31 robotaffichage
2023-02-02 Version finale du PCB de compteur de cerises
2023-02-02 Version finale du PCB du compteur de cerises
2023-02-02 Final Affichage
2023-02-02 docjauffrey
2023-02-03 rmoldPh
2023-02-05 uint32_tParser
2023-02-07 detection V2.1
2023-02-07 main board
2023-02-07 Version 1.0 du systeme de detection
2023-02-09 PCB_robot_ares
2023-02-12 pcb wifi V1
2023-02-12 clean
2023-02-13 majPCB
2023-02-16 ajout changement de strategie par reseau
    communication du wifi en serie par l'ESP vers le STM, puis remplacement de la strategie en cours, avec réponse lorsque tout est reçu
2023-03-07 majwifistrat
2023-03-07 majFonctionnel
2023-03-09 newmaj
2023-03-21 testPhob
2023-03-21 majValPhobos
2023-03-21 Communication des donnees a un ordinateur (SerialReader) et adaptation du lidar au PCB v2.1 (LIDAR_Ares_v1_2)
2023-03-26 AddHandleForwifiOrdr
2023-03-26 AddHandleForwifiOrdrV2
2023-03-26 AddHandleForwifiOrdrV3
2023-03-26 PrintWifi
2023-04-04 wifiDebughalfOk
2023-04-04 LIDAR_Ares_v1_3 : lidar 2Hz, 13 ROIs
2023-04-04 wifiV2
2023-04-12 Lecture UART lidar fonctionnelle avec remise a zero du buffer au bout de 2000 caracteres
2023-04-13 Interpretation lidar fonctionnelle et tentative lidar1.4 avec frequence plus elevee
2023-04-13 Lidar 1.4 fonctionnel et Code phobos avec temps d'arret acceptable. Fonctionne avec 15 capteurs et a vitesse moitie. Penser a augmenter la distance de blocage
2023-04-15 V2 mis a jour pour pre coupe
2023-04-16 ServerPy maj
2023-04-16 JustFormatingPythonServer
2023-04-21 Correction du code Arduino & PCB Cherrycount
2023-04-23 Commentaires et Rangement du lecteur serie du lidar (Code SerialReader & PhobosBoardWifiAndStratV2)
2023-04-27 maj avec l'ancienne version du code phobos
2023-04-27 maj ancien code ajout wifi, strat
2023-04-27 maj avec l'ancienne version dma
2023-05-15 cleaning com
2023-05-15 PCBRasp
2023-05-17 commande pour ax12
2023-05-17 ax12
2023-05-17 sert à rien
2023-05-17 wifiStratV3
2023-05-18 mainboardphobosSourcechnge
2023-05-18 majPointPhobosV2
2023-05-18 Lidar filtre forward/backward (indexes a verifier)
2023-05-18 PhobosMainBoard avec Lidar actif
2023-05-19 serie3
2023-05-19 Code final Cherrycount/ajout fichier step ax12
2023-05-19 serie4
2023-05-20 serie5
2023-05-21 marcheArrièreTest
2023-05-21 marcheArrireV2
2023-09-07 test asserv
2023-10-07 Schema de la trame du lidar pour correspondre au nombre reel d'octets envoyes
